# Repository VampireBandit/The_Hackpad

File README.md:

## The_Hackpad

A compact, programmable macropad built for custom key mappings, macros, and shortcuts. Designed for productivity, gaming, or media control with SEEDSTUDIO XIAO-RP2040-DP.

---

## Overview

-keys with customizable firmware

-RGB LED per-key illumination

-Rotary encoder for volume/scrolling

-Hot-swappable switches

-USB-C connectivity

-KMK compatible (or your firmware choice)

-Compact 4X3 layout

---

## Images

### PCB

### Schematic

### Overall

### USB Hole

---

This is my first time making a full on electronic project. Didn't know a single thing about PCB's,CAD or firmwares. This was pretty fun to make and Thanks to HackClub for this oppourtunity.

## BOM
- 1x  Seeed XIAO RP2040
- 12x through-hole 1N4148 Diodes
- 12x MX-Style switches
- 1x EC11 Rotary encoder
- 1x 0.91 inch OLED display 
- 4x SK6812 MINI-E LEDs
- 4x M3x16mm screws
- 4x M3x5mx4mm heatset inserts

check BOM.csv for more info.
---

## Firmware

Configured using KMK firmware. Can be used other firmwares though!

---

Made by Rubaiyat Islam

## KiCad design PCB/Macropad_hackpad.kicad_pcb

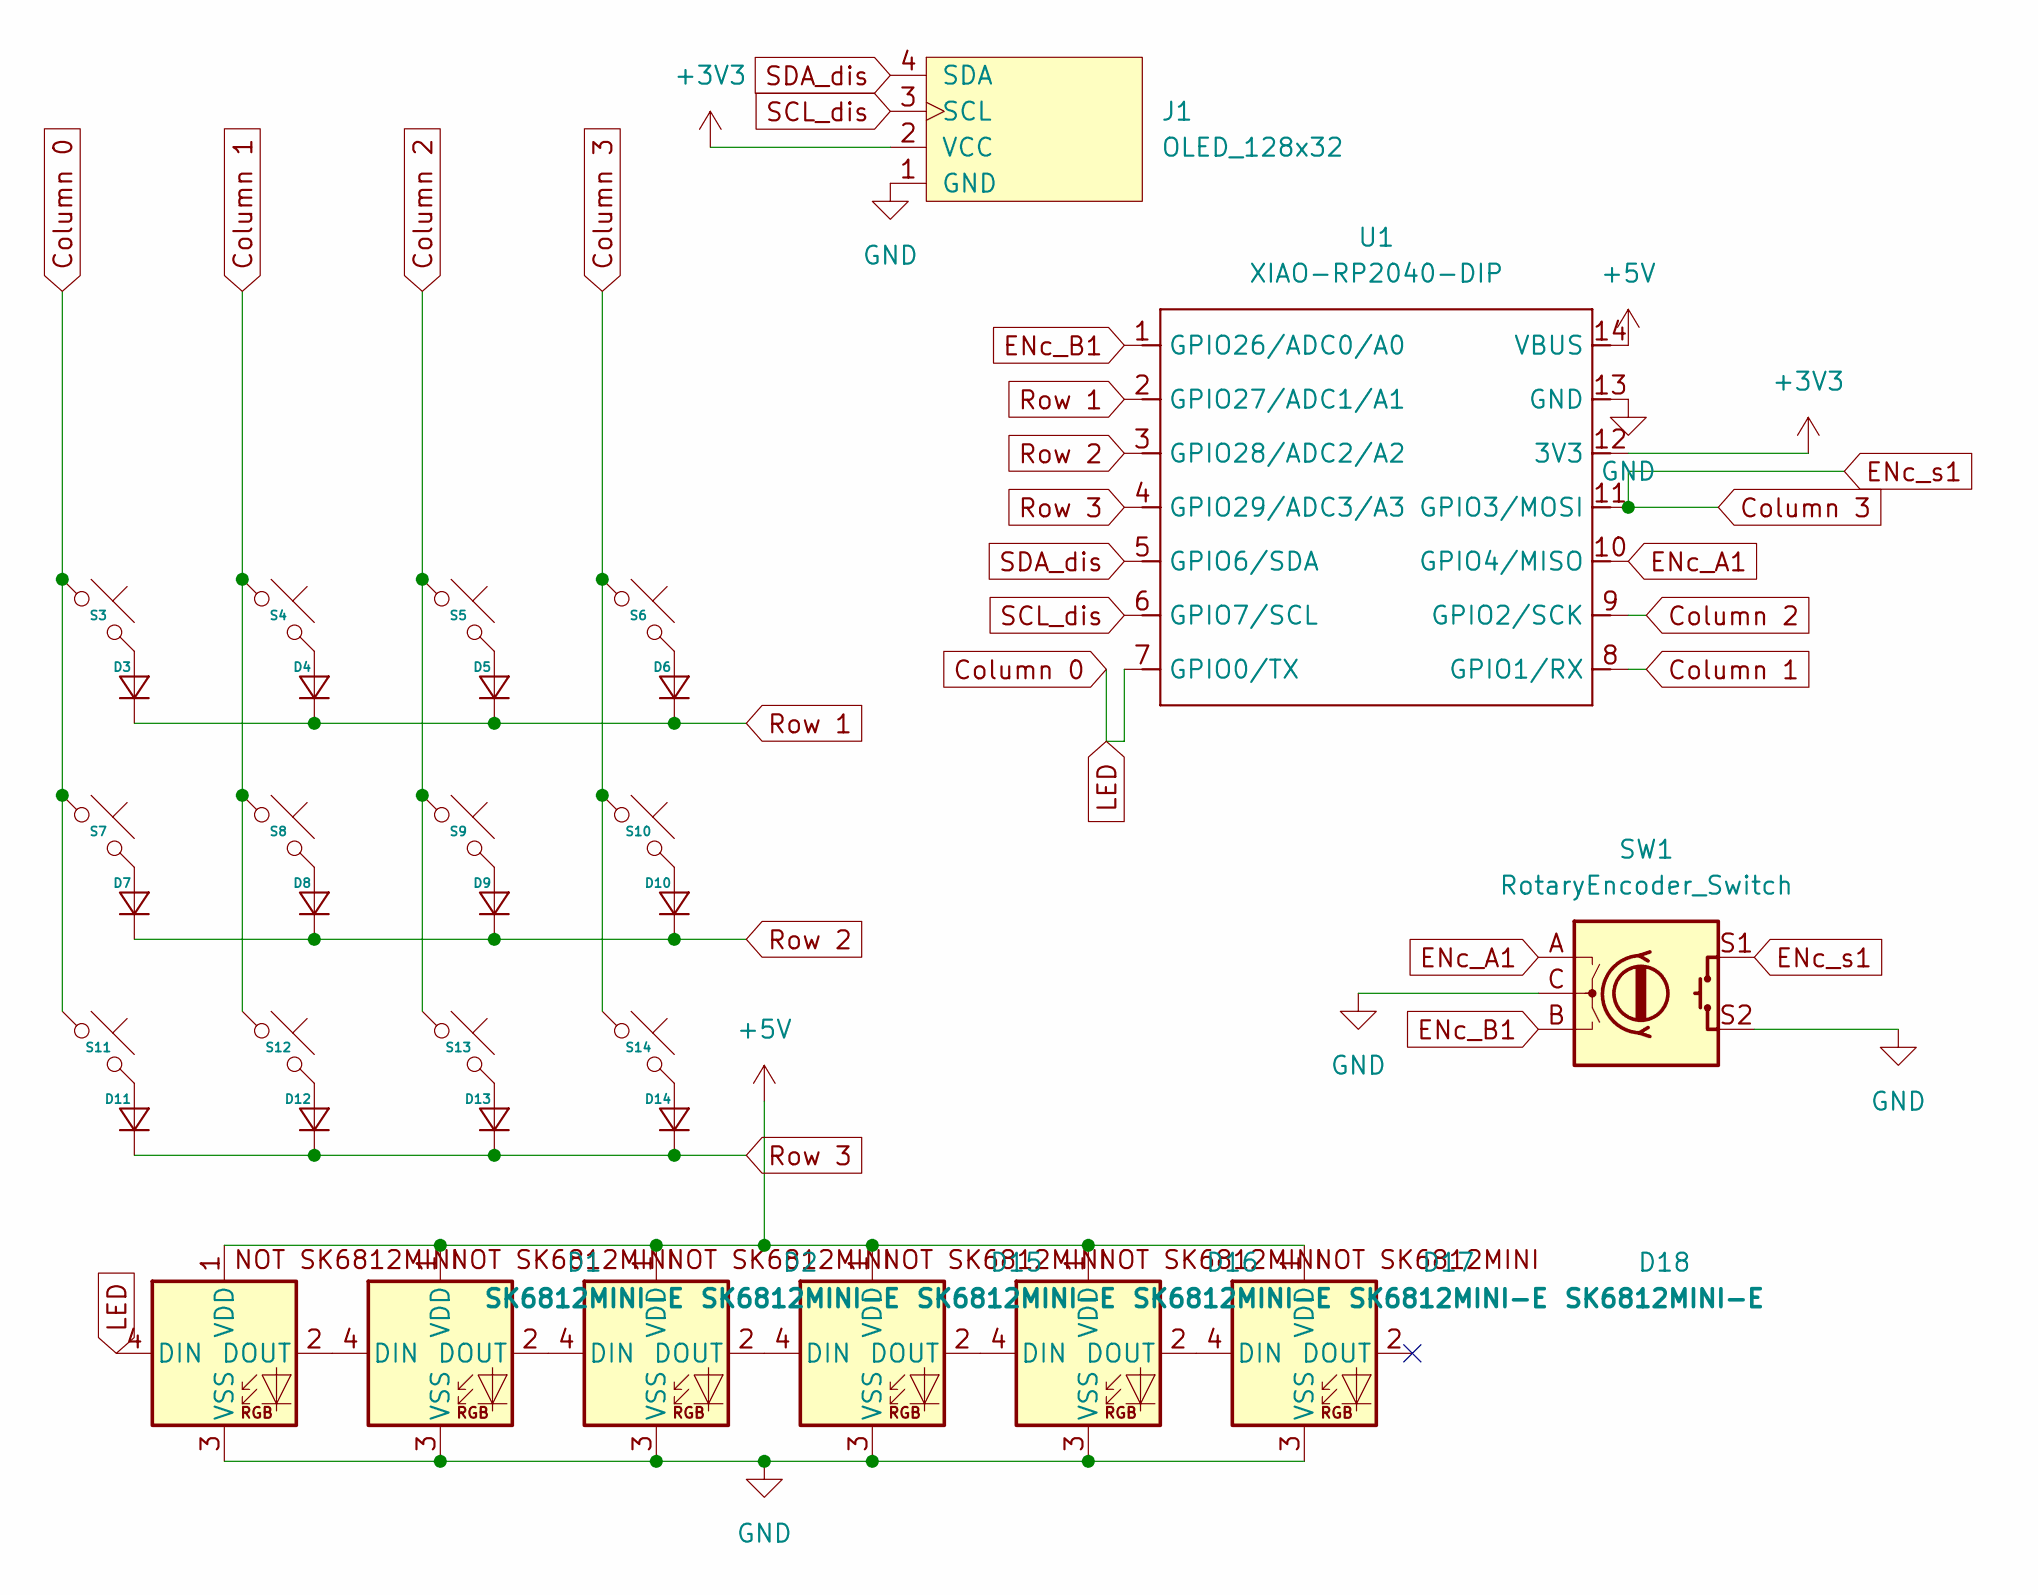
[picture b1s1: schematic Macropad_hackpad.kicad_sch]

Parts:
D1, D2, D15, D16, D17, D18: SK6812MINI-E; MX_SK6812MINI-E_REV
D3, D4, D5, D6, D7, D8, D9, D10, D11, D12, D13, D14: Diode_DO-35
J1: OLED_128x32
S3, S4, S5, S6, S7, S8, S9, S10, S11, S12, S13, S14: MX_PCB_1.00u
SW1: RotaryEncoder_Switch; RotaryEncoder_Alps_EC11E-Switch_Vertical_H20mm
U1: XIAO-RP2040-DIP

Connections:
+3V3: J1.2 (VCC), U1.12 (3V3)
+5V: D1.1 (VDD), D2.1 (VDD), D15.1 (VDD), D16.1 (VDD), D17.1 (VDD), D18.1 (VDD), U1.14 (VBUS)
Column 0: D1.4 (DIN), S3.1, S7.1, S11.1, U1.7 (GPIO0/TX)
Column 1: S4.1, S8.1, S12.1, U1.8 (GPIO1/RX)
Column 2: S5.1, S9.1, S13.1, U1.9 (GPIO2/SCK)
Column 3: S6.1, S10.1, S14.1, SW1.S1, U1.11 (GPIO3/MOSI)
ENc_A1: SW1.A, U1.10 (GPIO4/MISO)
ENc_B1: SW1.B, U1.1 (GPIO26/ADC0/A0)
GND: D1.3 (VSS), D2.3 (VSS), D15.3 (VSS), D16.3 (VSS), D17.3 (VSS), D18.3 (VSS), J1.1 (GND), SW1.C, SW1.S2, U1.13 (GND)
unnamed: D1.2 (DOUT), D2.4 (DIN)
unnamed: D3.2 (A), S3.2
unnamed: D4.2 (A), S4.2
unnamed: D5.2 (A), S5.2
unnamed: D6.2 (A), S6.2
unnamed: D7.2 (A), S7.2
unnamed: D8.2 (A), S8.2
unnamed: D9.2 (A), S9.2
unnamed: D10.2 (A), S10.2
unnamed: D11.2 (A), S11.2
unnamed: D12.2 (A), S12.2
unnamed: D13.2 (A), S13.2
unnamed: D14.2 (A), S14.2
unnamed: D2.2 (DOUT), D15.4 (DIN)
unnamed: D15.2 (DOUT), D16.4 (DIN)
unnamed: D16.2 (DOUT), D17.4 (DIN)
unnamed: D17.2 (DOUT), D18.4 (DIN)
Row 1: D3.1 (K), D4.1 (K), D5.1 (K), D6.1 (K), U1.2 (GPIO27/ADC1/A1)
Row 2: D7.1 (K), D8.1 (K), D9.1 (K), D10.1 (K), U1.3 (GPIO28/ADC2/A2)
Row 3: D11.1 (K), D12.1 (K), D13.1 (K), D14.1 (K), U1.4 (GPIO29/ADC3/A3)
SCL_dis: J1.3 (SCL), U1.6 (GPIO7/SCL)
SDA_dis: J1.4 (SDA), U1.5 (GPIO6/SDA)

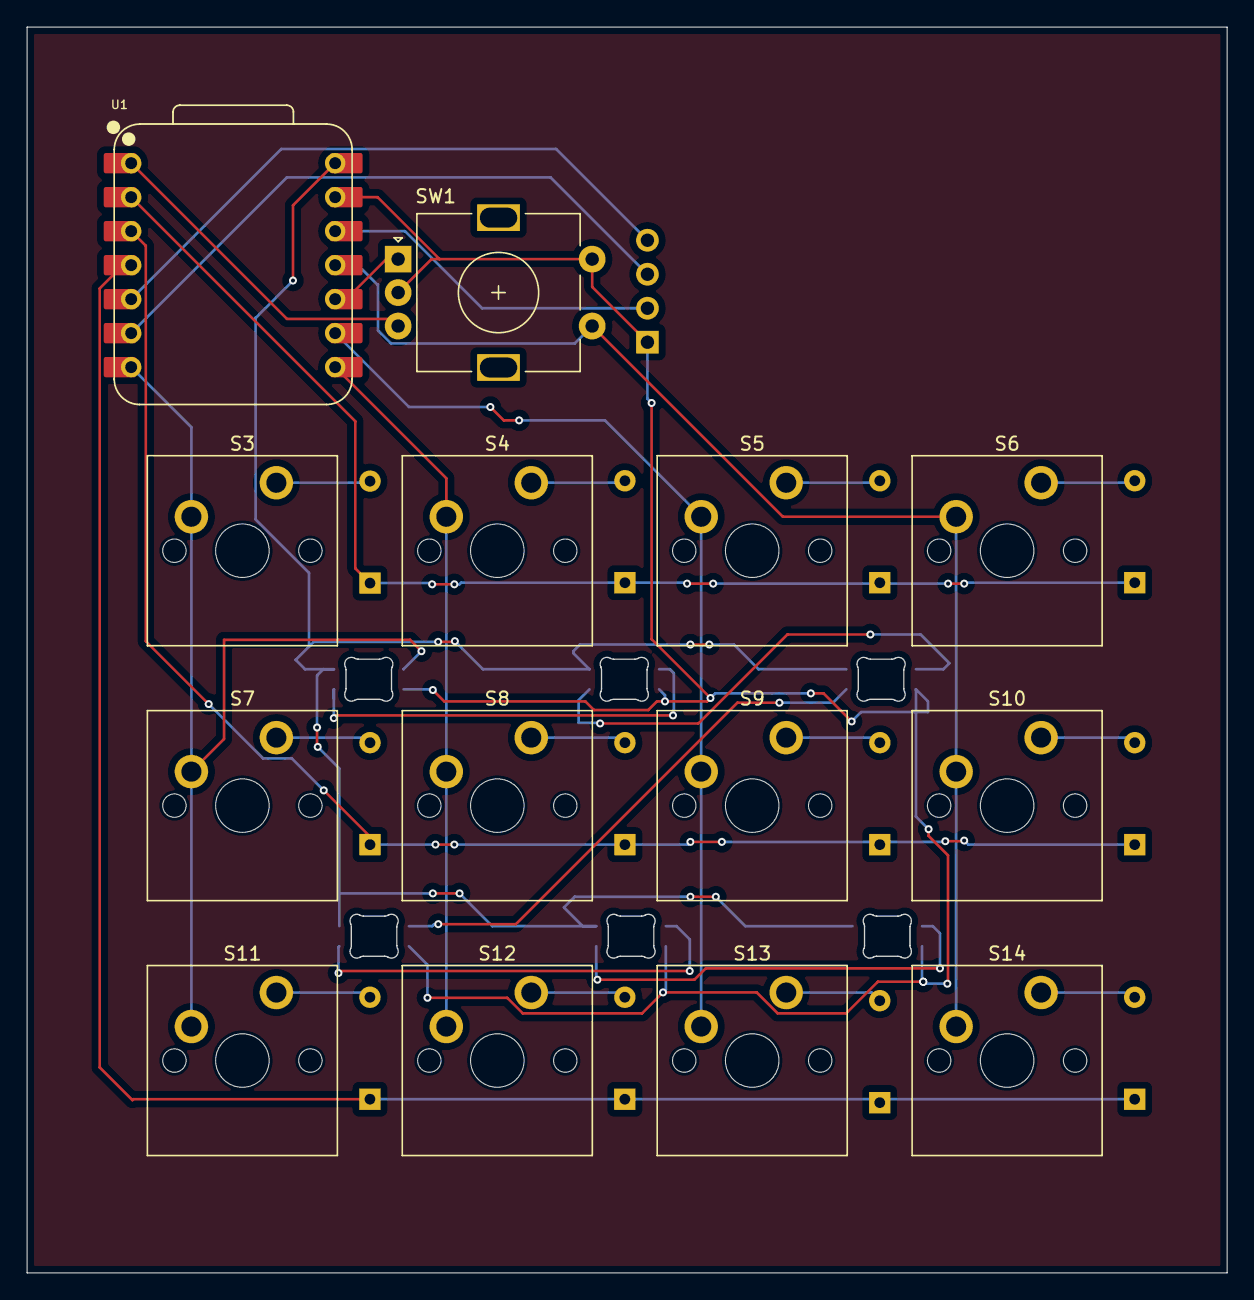
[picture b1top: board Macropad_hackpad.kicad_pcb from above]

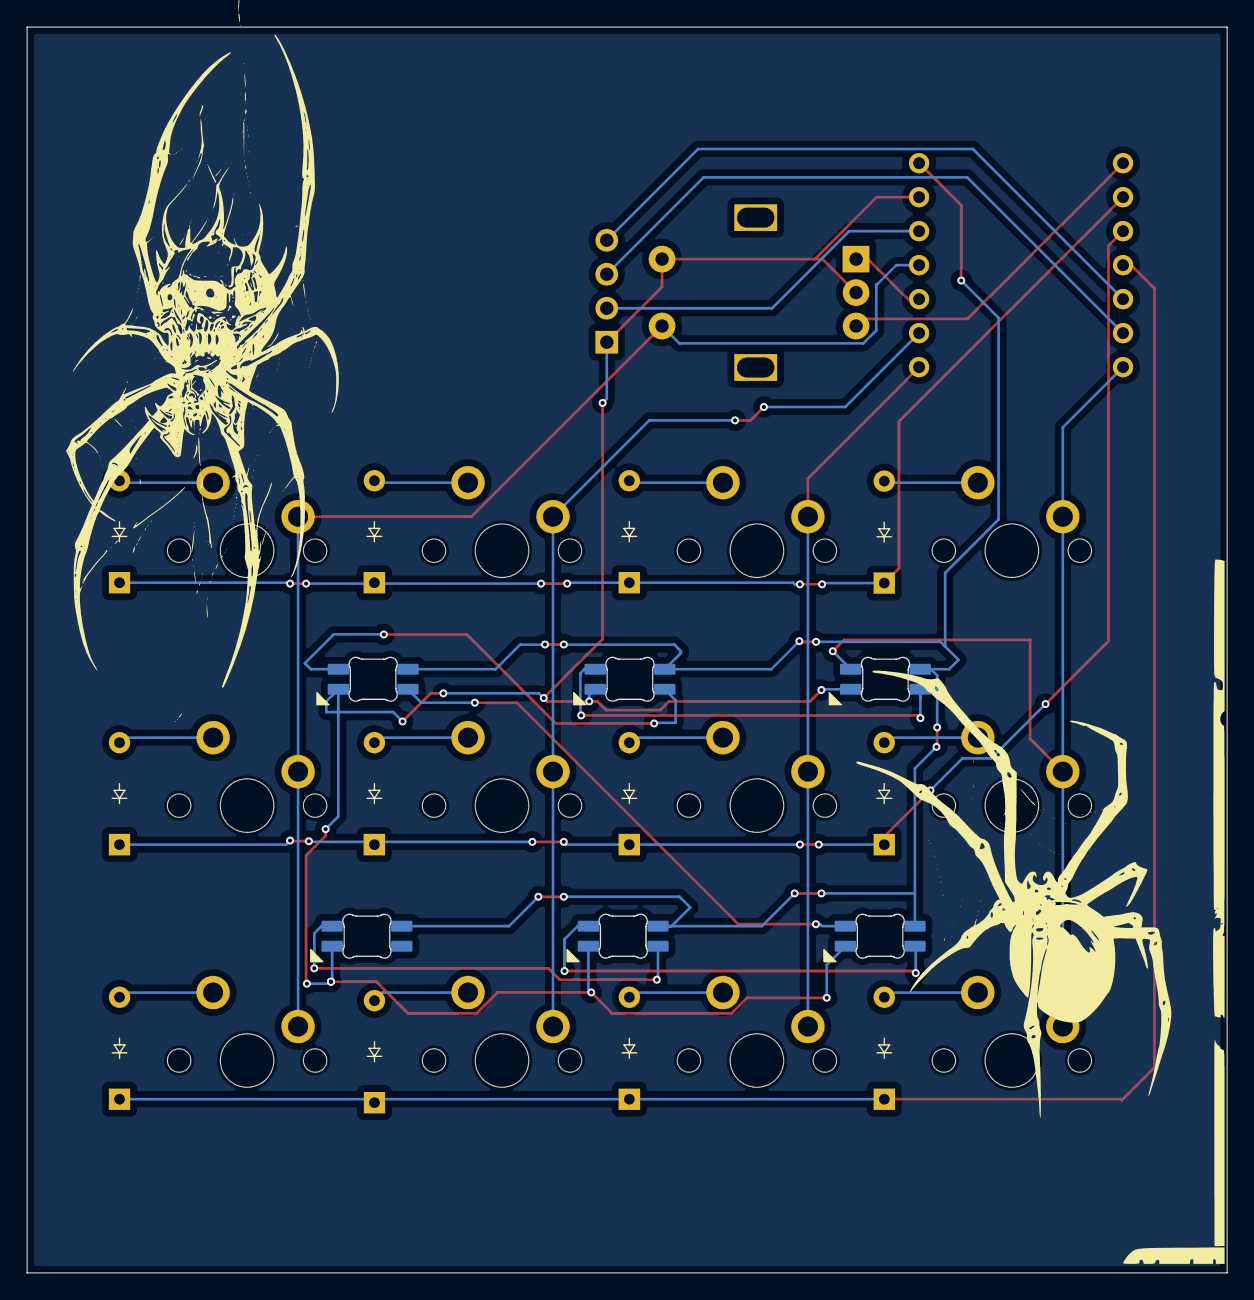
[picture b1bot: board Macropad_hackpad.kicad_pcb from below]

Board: 2 copper layers, 89.6 x 93.0 mm, 33 parts (12 on the bottom side), 31 nets.

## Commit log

2026-02-24 README.md
2026-02-28 Update README to reference BOM.csv
    Added a note to check BOM.csv for more information.
2026-03-03 Added clear pictures of the usb cutout
